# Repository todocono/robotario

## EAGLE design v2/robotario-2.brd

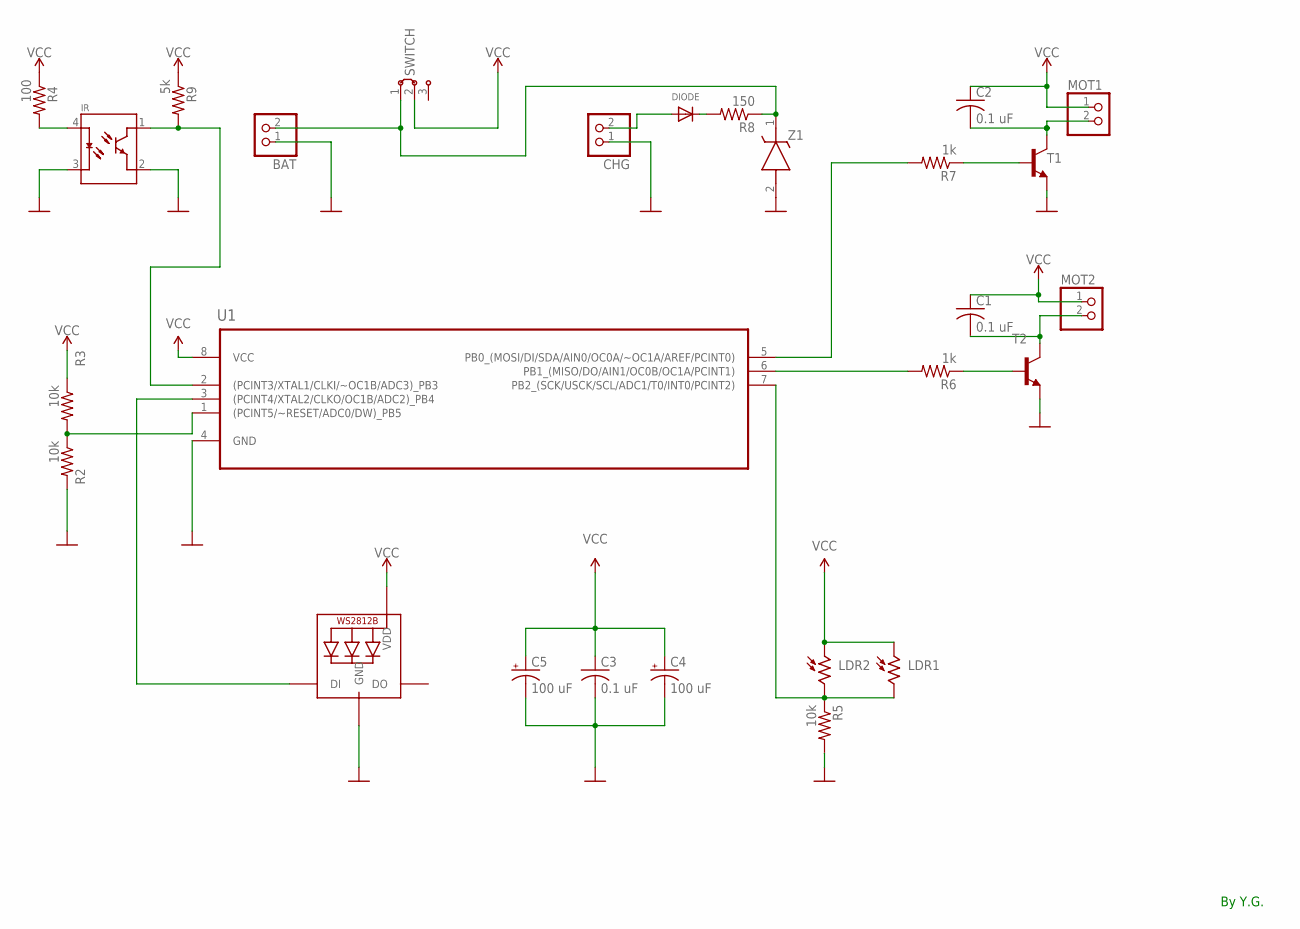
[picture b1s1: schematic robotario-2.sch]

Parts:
BAT: PINHD-1X2; 1X02
C1, C2, C3: 0.1 uF; C050-024X044
C4, C5: 100 uF; E5-5
CHG: PINHD-1X2; 1X02
DIODE: DIODEDO-1N4148; DO-1N4148
IR: TCRT5000L; XDCR_TCRT5000L
LDR1, LDR2: A1050_14; T0-46-A10XX
LED2: WS2812B5050; WS2812B
MOT1, MOT2: PINHD-1X2; 1X02
R2, R3, R5: 10k; 0207/10
R4: 100; 0207/10
R6, R7: 1k; 0207/10
R8: 150; 0207/10
R9: 5k; 0207/10
SWITCH: J2X2MM; 04C
T1, T2: 2N3904; TO92
U1: ATTINY85-20PU; DIP254P762X533-8
Z1: NZX4V3C; DIOAD950W60L350D150

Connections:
GND: BAT.1, C3.2, C4.-, C5.-, CHG.1, IR.2 (E), IR.3 (C), LED2.3-GND (GND), R2.2, R5.2, T1.3 (E), T2.3 (E), U1.4 (GND), Z1.2 (A)
unnamed: BAT.2, R8.1, SWITCH.1, Z1.1 (K)
unnamed: R6.1, T2.2 (B)
unnamed: R7.1, T1.2 (B)
unnamed: R2.1, R3.2, U1.1 ((PCINT5/~RESET/ADC0/DW)_PB5)
unnamed: IR.1 (CO), R9.2, U1.2 ((PCINT3/XTAL1/CLKI/~OC1B/ADC3)_PB3)
unnamed: LDR1.2, LDR2.2, R5.1, U1.7 (PB2_(SCK/USCK/SCL/ADC1/T0/INT0/PCINT2))
unnamed: C2.2, MOT1.2, T1.1 (C)
unnamed: CHG.2, DIODE.A
unnamed: LED2.4-DIN (DI), U1.3 ((PCINT4/XTAL2/CLKO/OC1B/ADC2)_PB4)
unnamed: C1.2, MOT2.2, T2.1 (C)
unnamed: R7.2, U1.5 (PB0_(MOSI/DI/SDA/AIN0/OC0A/~OC1A/AREF/P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)
unnamed: R6.2, U1.6 (PB1_(MISO/DO/AIN1/OC0B/OC1A/PCINT1))
unnamed: DIODE.C, R8.2
unnamed: IR.4 (A), R4.2
VCC: C1.1, C2.1, C3.1, C4.+, C5.+, LDR1.1, LDR2.1, LED2.1-VDD (VDD), MOT1.1, MOT2.1, R3.1, R4.1, R9.1, SWITCH.2, U1.8 (VCC)

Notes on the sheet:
By Y.G.

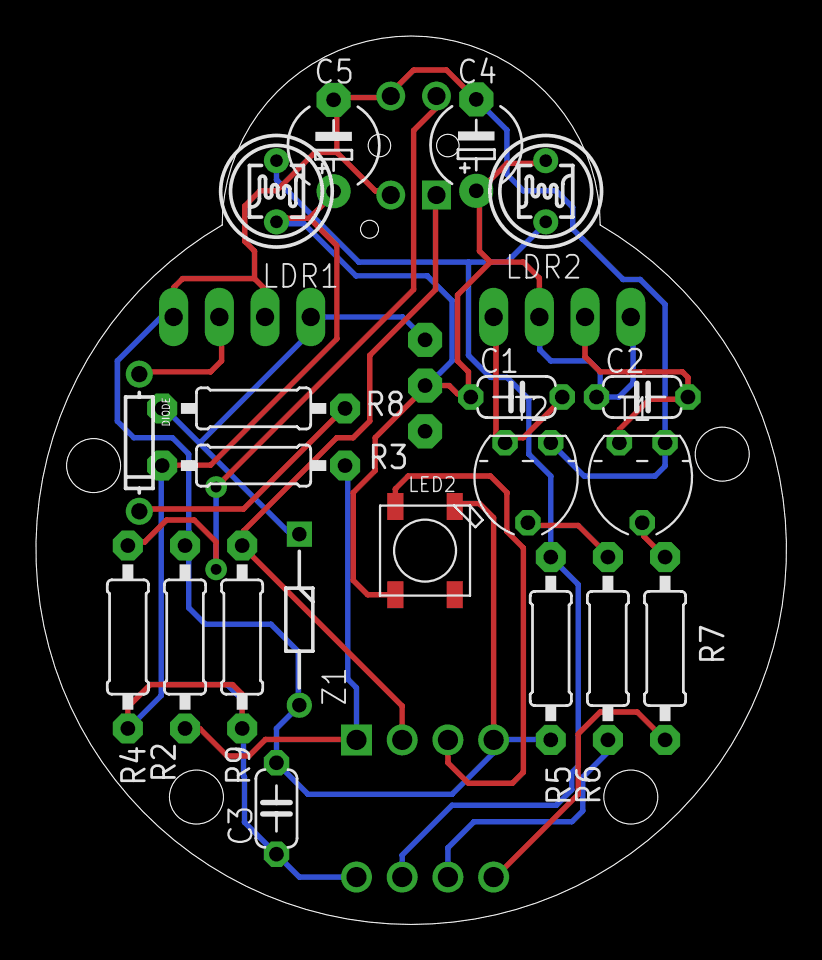
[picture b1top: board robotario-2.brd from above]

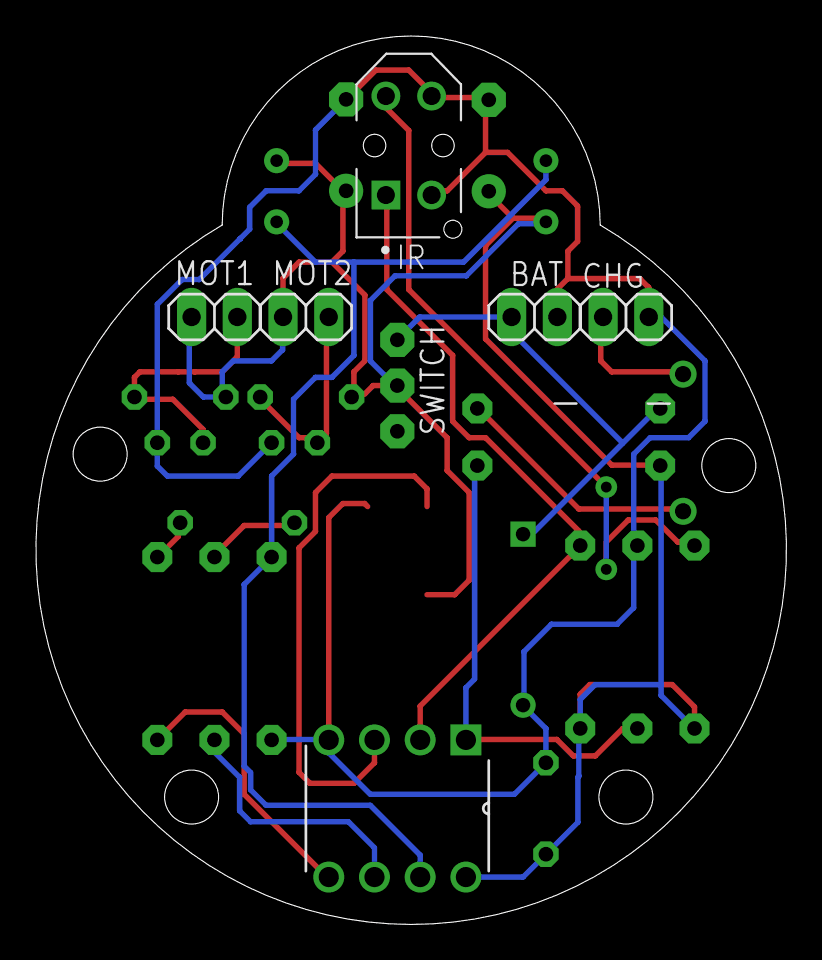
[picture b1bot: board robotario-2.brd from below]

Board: 2 copper layers, 41.7 x 49.4 mm, 27 parts (7 on the bottom side), 16 nets.

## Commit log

2019-11-16 first push
2019-11-16 3rd try
2019-11-19 added software tests
2019-11-19 changed resistor
2019-11-21 added datasheets
2019-11-22 charge test added
2019-11-22 charge added
2019-11-22 charge2 added
2019-11-27 exhibition
2019-12-12 code improved by Y.Garg for IMA show

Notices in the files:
parts and their libraries:
SparkFun-PowerSymbols: Licensing: Creative Commons ShareAlike 4.0 International - https://creativecommons.org/licenses/by-sa/4.0
